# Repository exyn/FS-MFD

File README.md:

## FS-MFD
Simple USB Flight-Simulator MFD designed with KiCad for use with DCS/MSFS. Cheaper than commercial alternatives and every possibility to customise.<br>
Easy-to-get components, and everything through-hole, to make it easy to solder for anyone.<br>
One board with all components and the PCB ordered and delivered from JLCPCB was about $21 for our first run.<br>
Accompanying 3D-printable enclosure (see Mechanics).<br>

#### Features:

* 20 x Tactile Switches (Buttons)
* 2 x Rotary Encoder (with push-button)
* 2 x Toggle Switch/Slide Switch
* Raspberry Pi Pico control board/USB interface
* Simple SW project for use as a general Gamepad USB device available as source and binary.
<br>
For any questions send an e-mail to gustaf.lindstroem@gmail.com. There will be more projects to come.<br>
There might be a future version of this board with display (as an option maybe). It's designed with VR use in mind first though.
Should you have any specific modification request send it to us and we'll see what we can do.<br>
If our material is used for anything please give a simple credit by linking here. Everything is open to use, modify etc. of course though. Only requirement is that the derivative works is also released open source to the public.
<br><br>

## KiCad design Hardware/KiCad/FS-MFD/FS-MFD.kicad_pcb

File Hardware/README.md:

## Hardware

KiCad project and exported Gerber files to use directly to order boards.

* Two-layer board, 142x142 mm, nothing special or unusual regarding vias, traces, pads, drilling or otherwise.
* Gerber/drill files have been used with JLCPCB to order PCB:s that are exactly as expected (their default options for a two-layer board, only thing requested was black solder-mask.
* The Gerber/drill files currently uploaded correspond to revision A of the board. There are a couple of minor changes that will be made in revision B that should make it into any files used to make PCB:s. It is nothing fatal but especially the toggle switch footprints need to be changed.
* The KiCad project also is at revision A. See above comment.
* There is a BOM generated with KiCad. The board works with many different manufacturers of cheap switches for instance though so it's worth checking out before getting anything more expensive. Same thing regarding the EC11 encoders. A big point here was to do a simple and cheap board to make it as available as possible.
* There might be a future revision prepared for a display, that has not really been decided yet though since this board is meant for VR first.
* The libraries imported to the project will be put in a libraries directory to make things a bit cleaner. Expect most of these minor things in a revision B update coming soon.

<br>

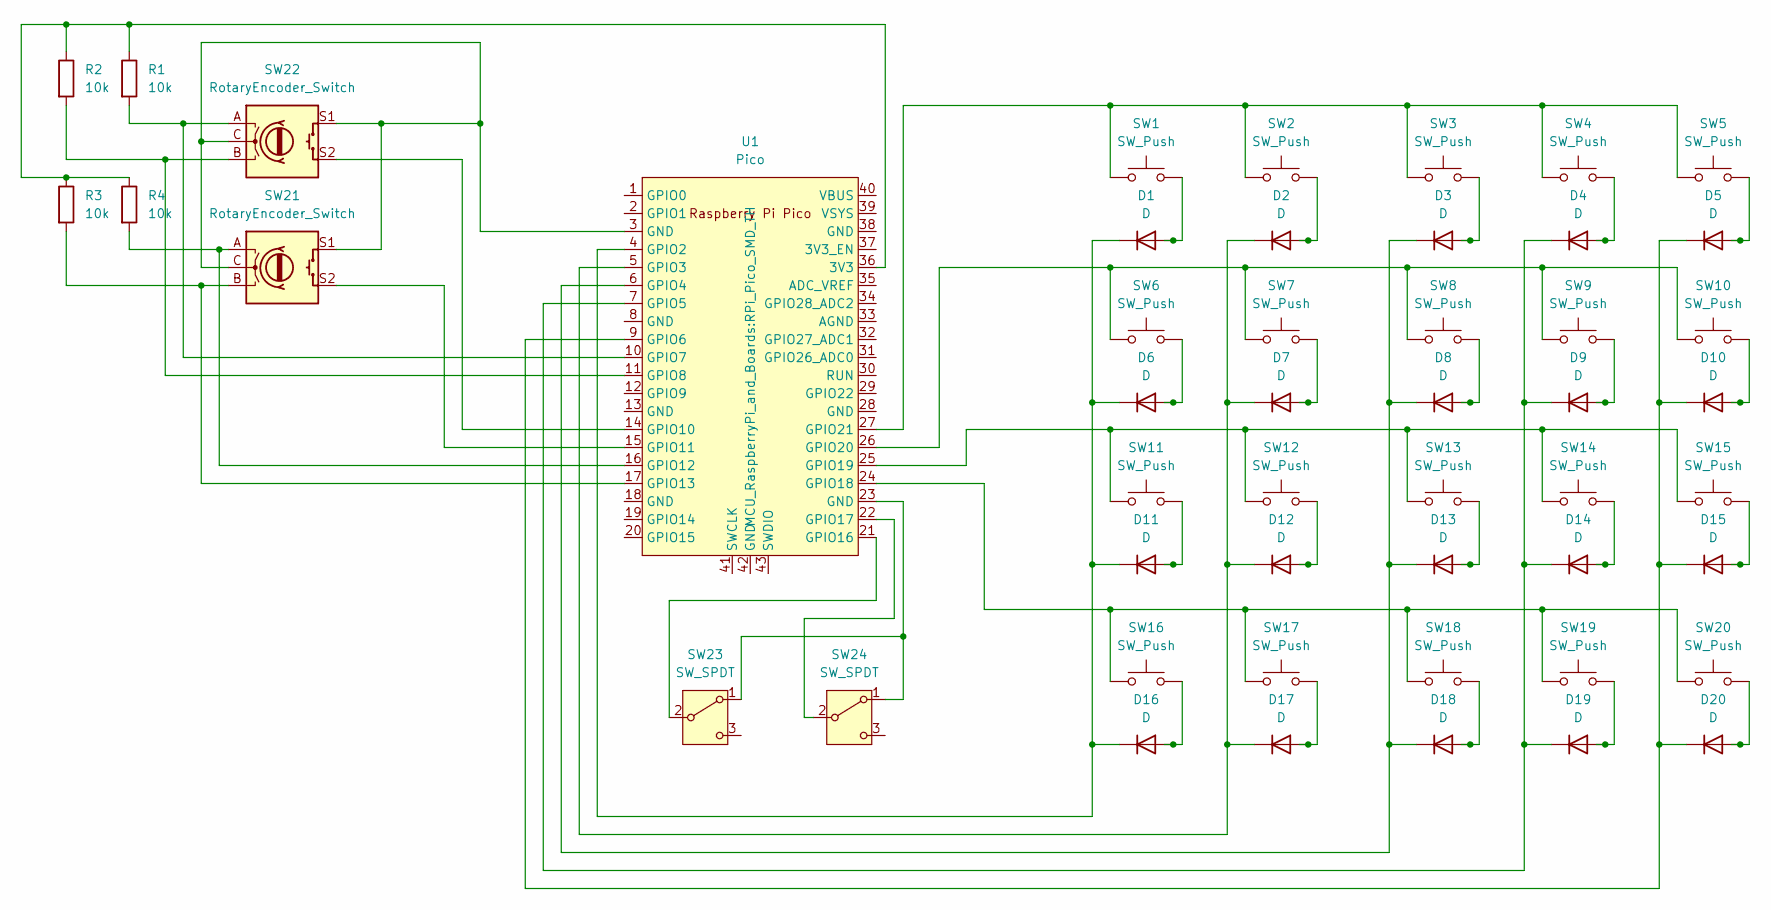
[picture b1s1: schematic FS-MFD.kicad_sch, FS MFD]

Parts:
D1, D2, D3, D4, D5, D6, D7, D8, D9, D10, D11, D12, D13, D14, D15, D16, D17, D18, D19, D20: D; D_A-405_P10.16mm_Horizontal
R1, R2, R3, R4: 10k; R_Axial_DIN0204_L3.6mm_D1.6mm_P5.08mm_Horizontal
SW1, SW2, SW3, SW4, SW5, SW6, SW7, SW8, SW9, SW10, SW11, SW12, SW13, SW14, SW15, SW16, SW17, SW18, SW19, SW20: SW_Push; SW_PUSH-12mm
SW21, SW22: RotaryEncoder_Switch; RotaryEncoder_Alps_EC11E-Switch_Vertical_H20mm
SW23, SW24: SW_SPDT; SW_100SP1T1B4M2QE
U1: Pico; RPi_Pico_SMD_TH

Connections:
unnamed: D1.2 (A), SW1.2
unnamed: D1.1 (K), D6.1 (K), D11.1 (K), D16.1 (K), U1.4 (GPIO2)
unnamed: D2.2 (A), SW2.2
unnamed: D3.2 (A), SW3.2
unnamed: D4.2 (A), SW4.2
unnamed: D5.2 (A), SW5.2
unnamed: D6.2 (A), SW6.2
unnamed: D7.2 (A), SW7.2
unnamed: D8.2 (A), SW8.2
unnamed: D9.2 (A), SW9.2
unnamed: D10.2 (A), SW10.2
unnamed: D5.1 (K), D10.1 (K), D15.1 (K), D20.1 (K), U1.9 (GPIO6)
unnamed: D11.2 (A), SW11.2
unnamed: D12.2 (A), SW12.2
unnamed: D2.1 (K), D7.1 (K), D12.1 (K), D17.1 (K), U1.5 (GPIO3)
unnamed: D13.2 (A), SW13.2
unnamed: D3.1 (K), D8.1 (K), D13.1 (K), D18.1 (K), U1.6 (GPIO4)
unnamed: D14.2 (A), SW14.2
unnamed: D4.1 (K), D9.1 (K), D14.1 (K), D19.1 (K), U1.7 (GPIO5)
unnamed: D15.2 (A), SW15.2
unnamed: D16.2 (A), SW16.2
unnamed: D17.2 (A), SW17.2
unnamed: D18.2 (A), SW18.2
unnamed: D19.2 (A), SW19.2
unnamed: D20.2 (A), SW20.2
unnamed: SW21.C, SW21.S1, SW22.C, SW22.S1, U1.3 (GND)
unnamed: SW23.1 (A), SW24.1 (A), U1.23 (GND)
unnamed: SW23.2 (B), U1.21 (GPIO16)
unnamed: SW24.2 (B), U1.22 (GPIO17)
unnamed: R1.1, R2.1, R3.1, R4.1, U1.36 (3V3)
unnamed: R1.2, SW22.A, U1.10 (GPIO7)
unnamed: R2.2, SW22.B, U1.11 (GPIO8)
unnamed: SW22.S2, U1.14 (GPIO10)
unnamed: SW21.S2, U1.15 (GPIO11)
unnamed: R4.2, SW21.A, U1.16 (GPIO12)
unnamed: R3.2, SW21.B, U1.17 (GPIO13)
unnamed: SW16.1, SW17.1, SW18.1, SW19.1, SW20.1, U1.24 (GPIO18)
unnamed: SW11.1, SW12.1, SW13.1, SW14.1, SW15.1, U1.25 (GPIO19)
unnamed: SW6.1, SW7.1, SW8.1, SW9.1, SW10.1, U1.26 (GPIO20)
unnamed: SW1.1, SW2.1, SW3.1, SW4.1, SW5.1, U1.27 (GPIO21)

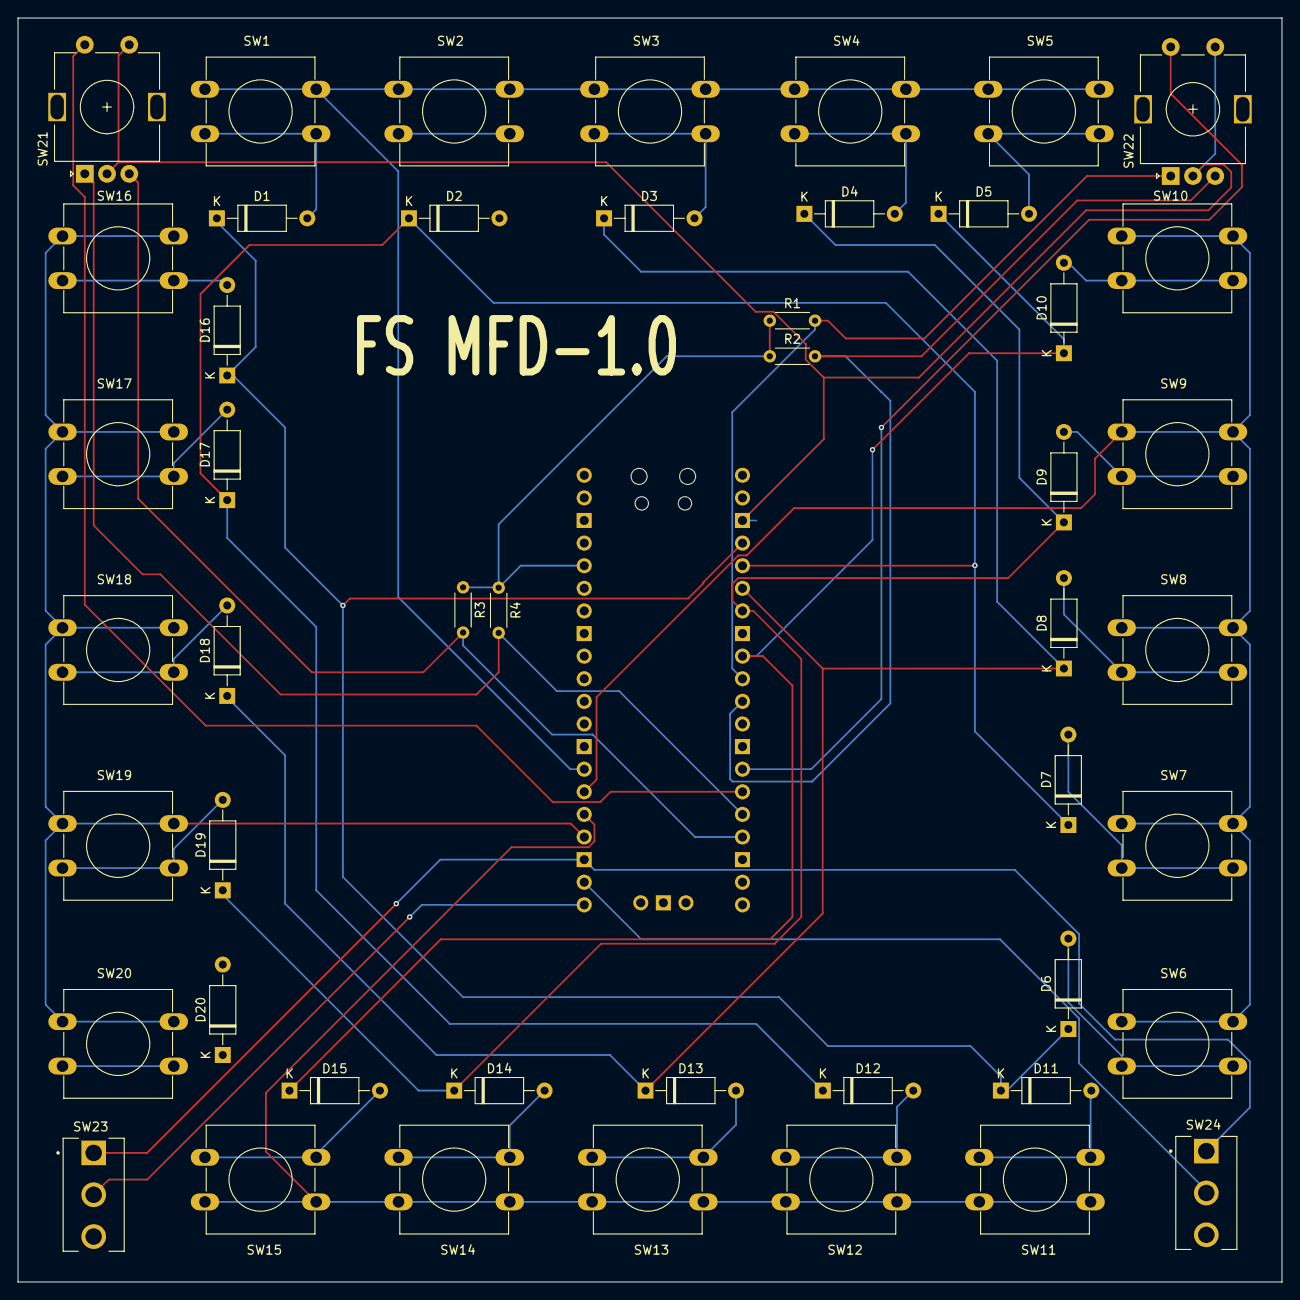
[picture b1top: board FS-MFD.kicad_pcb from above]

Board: 2 copper layers, 142.0 x 142.0 mm, 49 parts (1 on the bottom side), 40 nets.

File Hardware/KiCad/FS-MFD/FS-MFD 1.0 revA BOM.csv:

"Reference","Value","Datasheet","Footprint","Qty","DNP"
"D1,D2,D3,D4,D5,D6,D7,D8,D9,D10,D11,D12,D13,D14,D15,D16,D17,D18,D19,D20","D","~","Diode_THT:D_A-405_P10.16mm_Horizontal","20",""
"R1,R2,R3,R4","10k","~","Resistor_THT:R_Axial_DIN0204_L3.6mm_D1.6mm_P5.08mm_Horizontal","4",""
"SW1,SW2,SW3,SW4,SW5,SW6,SW7,SW8,SW9,SW10,SW11,SW12,SW13,SW14,SW15,SW16,SW17,SW18,SW19,SW20","SW_Push","~","Button_Switch_THT:SW_PUSH-12mm","20",""
"SW21,SW22","RotaryEncoder_Switch","~","Rotary_Encoder:RotaryEncoder_Alps_EC11E-Switch_Vertical_H20mm","2",""
"SW23,SW24","SW_SPDT","~","100SP1T1B4M2QE:SW_100SP1T1B4M2QE","2",""
"U1","Pico","","MCU_RaspberryPi_and_Boards:RPi_Pico_SMD_TH","1",""

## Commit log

2024-07-26 Update README.md
    README.md first draft.
2024-07-26 Create README.md
    Make place for KiCad project.
2024-07-26 Create README.md
    Software README.md first draft.
2024-07-26 Create README.md
    Mechanics README.md first draft.
2024-07-26 Update README.md
    Some minor format editing.
2024-07-26 Update README.md
    Additional format editing..
2024-07-26 Update README.md
    Image added to main README.md (for now).
2024-07-26 Update README.md
    Smaller image of board.
2024-08-01 Add files via upload
    Add a first look of the main part of the mechanics.
2024-08-01 Update README.md
    Add a first picture of the mechanics.
2024-08-01 Update README.md
    First test firmware has been written and tested.
2024-08-01 Update README.md
    Give a sense of the cost per board.
2024-08-01 Update README.md
    Add e-mail for any questions.
2024-08-02 Update README.md
    Minor expression edit..
2024-08-02 Add files via upload
    Remove background.
2024-08-02 Update README.md
    Remove image background..
2024-08-03 Add KiCad project
2024-08-03 Add ploted Gerber and drill files
    These files correspond with the first PCB:s produced, revision A, and there are at least two minor things to change there.
    Nothing that means connections are wrong or something else more serious though. See revision B of the board for details.
2024-08-03 Update README.md
    Some spelling etc.
2024-08-03 Update README.md
    Clarification.
2024-08-03 Update README.md
    Some more details..
2024-08-03 Update README.md
    "Formatting" :)
2024-08-03 Update README.md
    BOM
2024-08-03 Update README.md
    Display, possibly, maybe, at some point.
2024-08-03 Add files via upload
    Add basic BOM. Will be updated with correct references to the Würth buttons/caps for instance but this is a start.
2024-08-04 Add files via upload
    Enclosure almost done.
